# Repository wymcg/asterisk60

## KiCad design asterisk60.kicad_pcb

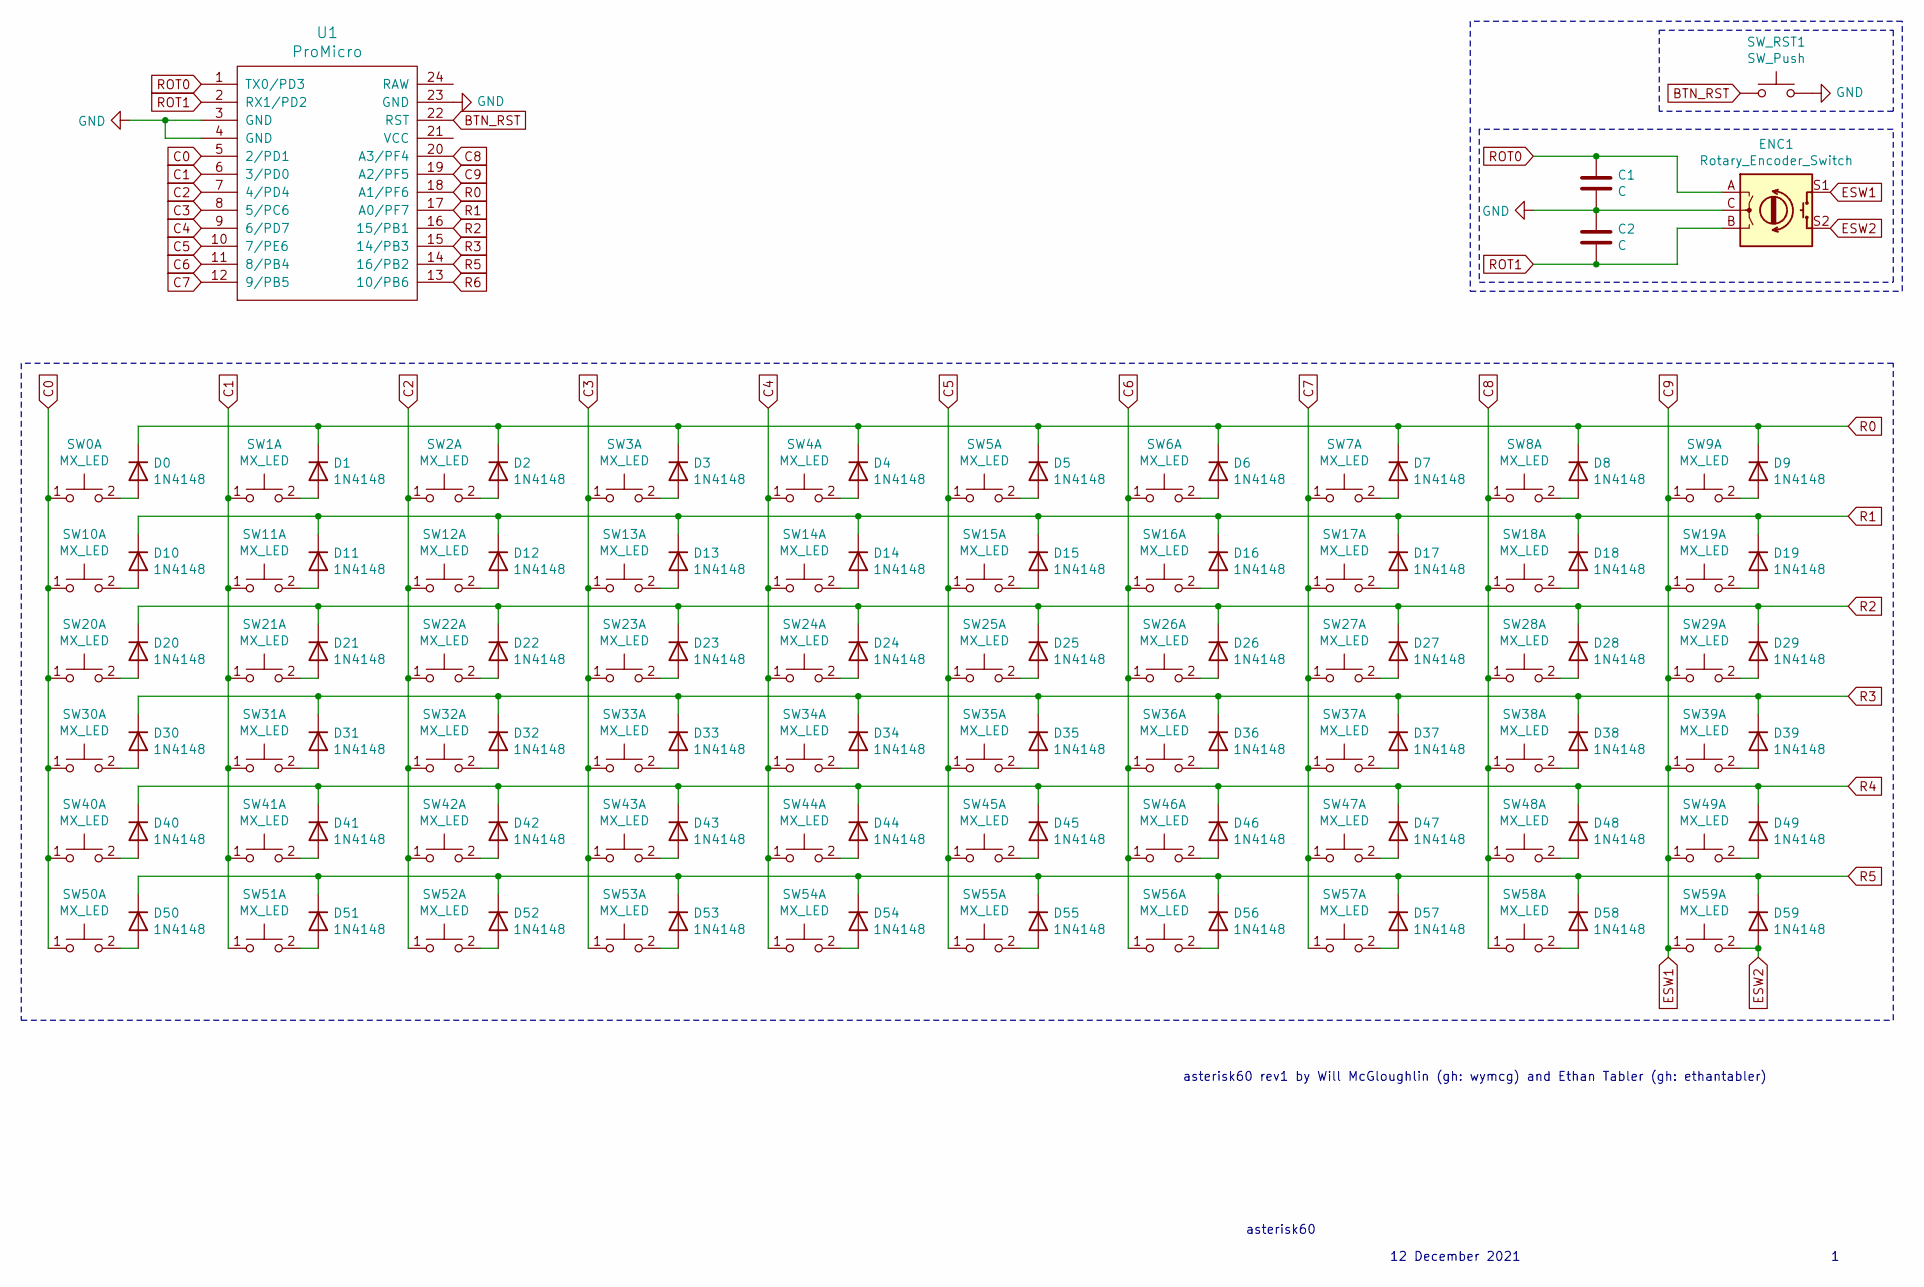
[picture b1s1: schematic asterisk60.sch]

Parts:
C1, C2: C; C_0603
D0, D1, D2, D3, D4, D5, D6, D7, D8, D9, D10, D11, D12, D13, D14, D15, D16, D17, D18, D19, D20, D21, D22, D23, D24, D25, D26, D27, D28, D29, D30, D31, D32, D33, D34, D35, D36, D37, D38, D39, D40, D41, D42, D43, D44, D45, D46, D47, D48, D49, D50, D51, D52, D53, D54, D55, D56, D57, D58, D59: 1N4148; D_DO-35_SOD27_P7.62mm_Horizontal
ENC1: Rotary_Encoder_Switch; RotaryEncoder_EC11
SW0, SW1, SW2, SW3, SW4, SW5, SW6, SW7, SW8, SW9, SW10, SW11, SW12, SW13, SW14, SW15, SW16, SW17, SW18, SW19, SW20, SW21, SW22, SW23, SW24, SW25, SW26, SW27, SW28, SW29, SW30, SW31, SW32, SW33, SW34, SW35, SW36, SW37, SW38, SW39, SW40, SW41, SW42, SW43, SW44, SW45, SW46, SW47, SW48, SW49, SW50, SW51, SW52, SW53, SW54, SW55, SW56, SW57, SW58, SW59: MX_LED; SW_Cherry_MX_1.00u_PCB
SW_RST1: SW_Push; SW_SPST_TL3342
U1: ProMicro; ArduinoProMicro

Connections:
BTN_RST: SW_RST1.1, U1.22 (RST)
C0: SW0.1, SW10.1, SW20.1, SW30.1, SW40.1, SW50.1, U1.5 (2/PD1)
C1: SW1.1, SW11.1, SW21.1, SW31.1, SW41.1, SW51.1, U1.6 (3/PD0)
C2: SW2.1, SW12.1, SW22.1, SW32.1, SW42.1, SW52.1, U1.7 (4/PD4)
C3: SW3.1, SW13.1, SW23.1, SW33.1, SW43.1, SW53.1, U1.8 (5/PC6)
C4: SW4.1, SW14.1, SW24.1, SW34.1, SW44.1, SW54.1, U1.9 (6/PD7)
C5: SW5.1, SW15.1, SW25.1, SW35.1, SW45.1, SW55.1, U1.10 (7/PE6)
C6: SW6.1, SW16.1, SW26.1, SW36.1, SW46.1, SW56.1, U1.11 (8/PB4)
C7: SW7.1, SW17.1, SW27.1, SW37.1, SW47.1, SW57.1, U1.12 (9/PB5)
C8: SW8.1, SW18.1, SW28.1, SW38.1, SW48.1, SW58.1, U1.20 (A3/PF4)
C9: ENC1.S1, SW9.1, SW19.1, SW29.1, SW39.1, SW49.1, SW59.1, U1.19 (A2/PF5)
ESW2: D59.2 (A), ENC1.S2, SW59.2
GND: C1.2, C2.1, ENC1.C, SW_RST1.2, U1.3 (GND), U1.4 (GND), U1.23 (GND)
unnamed: D0.2 (A), SW0.2
unnamed: D1.2 (A), SW1.2
unnamed: D2.2 (A), SW2.2
unnamed: D3.2 (A), SW3.2
unnamed: D4.2 (A), SW4.2
unnamed: D5.2 (A), SW5.2
unnamed: D6.2 (A), SW6.2
unnamed: D7.2 (A), SW7.2
unnamed: D8.2 (A), SW8.2
unnamed: D9.2 (A), SW9.2
unnamed: D10.2 (A), SW10.2
unnamed: D11.2 (A), SW11.2
unnamed: D12.2 (A), SW12.2
unnamed: D13.2 (A), SW13.2
unnamed: D14.2 (A), SW14.2
unnamed: D15.2 (A), SW15.2
unnamed: D16.2 (A), SW16.2
unnamed: D17.2 (A), SW17.2
unnamed: D18.2 (A), SW18.2
unnamed: D19.2 (A), SW19.2
unnamed: D20.2 (A), SW20.2
unnamed: D21.2 (A), SW21.2
unnamed: D22.2 (A), SW22.2
unnamed: D23.2 (A), SW23.2
unnamed: D24.2 (A), SW24.2
unnamed: D25.2 (A), SW25.2
unnamed: D26.2 (A), SW26.2
unnamed: D27.2 (A), SW27.2
unnamed: D28.2 (A), SW28.2
unnamed: D29.2 (A), SW29.2
unnamed: D30.2 (A), SW30.2
unnamed: D31.2 (A), SW31.2
unnamed: D32.2 (A), SW32.2
unnamed: D33.2 (A), SW33.2
unnamed: D34.2 (A), SW34.2
unnamed: D35.2 (A), SW35.2
unnamed: D36.2 (A), SW36.2
unnamed: D37.2 (A), SW37.2
unnamed: D38.2 (A), SW38.2
unnamed: D39.2 (A), SW39.2
unnamed: D40.2 (A), SW40.2
unnamed: D41.2 (A), SW41.2
unnamed: D42.2 (A), SW42.2
unnamed: D43.2 (A), SW43.2
unnamed: D44.2 (A), SW44.2
unnamed: D45.2 (A), SW45.2
unnamed: D46.2 (A), SW46.2
unnamed: D47.2 (A), SW47.2
unnamed: D48.2 (A), SW48.2
unnamed: D49.2 (A), SW49.2
unnamed: D50.2 (A), SW50.2
unnamed: D51.2 (A), SW51.2
unnamed: D52.2 (A), SW52.2
unnamed: D53.2 (A), SW53.2
unnamed: D54.2 (A), SW54.2
unnamed: D55.2 (A), SW55.2
unnamed: D56.2 (A), SW56.2
unnamed: D57.2 (A), SW57.2
unnamed: D58.2 (A), SW58.2
R0: D0.1 (K), D1.1 (K), D2.1 (K), D3.1 (K), D4.1 (K), D5.1 (K), D6.1 (K), D7.1 (K), D8.1 (K), D9.1 (K), U1.18 (A1/PF6)
R1: D10.1 (K), D11.1 (K), D12.1 (K), D13.1 (K), D14.1 (K), D15.1 (K), D16.1 (K), D17.1 (K), D18.1 (K), D19.1 (K), U1.17 (A0/PF7)
R2: D20.1 (K), D21.1 (K), D22.1 (K), D23.1 (K), D24.1 (K), D25.1 (K), D26.1 (K), D27.1 (K), D28.1 (K), D29.1 (K), U1.16 (15/PB1)
R3: D30.1 (K), D31.1 (K), D32.1 (K), D33.1 (K), D34.1 (K), D35.1 (K), D36.1 (K), D37.1 (K), D38.1 (K), D39.1 (K), U1.15 (14/PB3)
R4: D40.1 (K), D41.1 (K), D42.1 (K), D43.1 (K), D44.1 (K), D45.1 (K), D46.1 (K), D47.1 (K), D48.1 (K), D49.1 (K)
R5: D50.1 (K), D51.1 (K), D52.1 (K), D53.1 (K), D54.1 (K), D55.1 (K), D56.1 (K), D57.1 (K), D58.1 (K), D59.1 (K), U1.14 (16/PB2)
R6: U1.13 (10/PB6)
ROT0: C1.1, ENC1.A, U1.1 (TX0/PD3)
ROT1: C2.2, ENC1.B, U1.2 (RX1/PD2)

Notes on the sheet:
asterisk60
12 December 2021
asterisk60 rev1 by Will McGloughlin (gh: wymcg) and Ethan Tabler (gh: ethantabler)

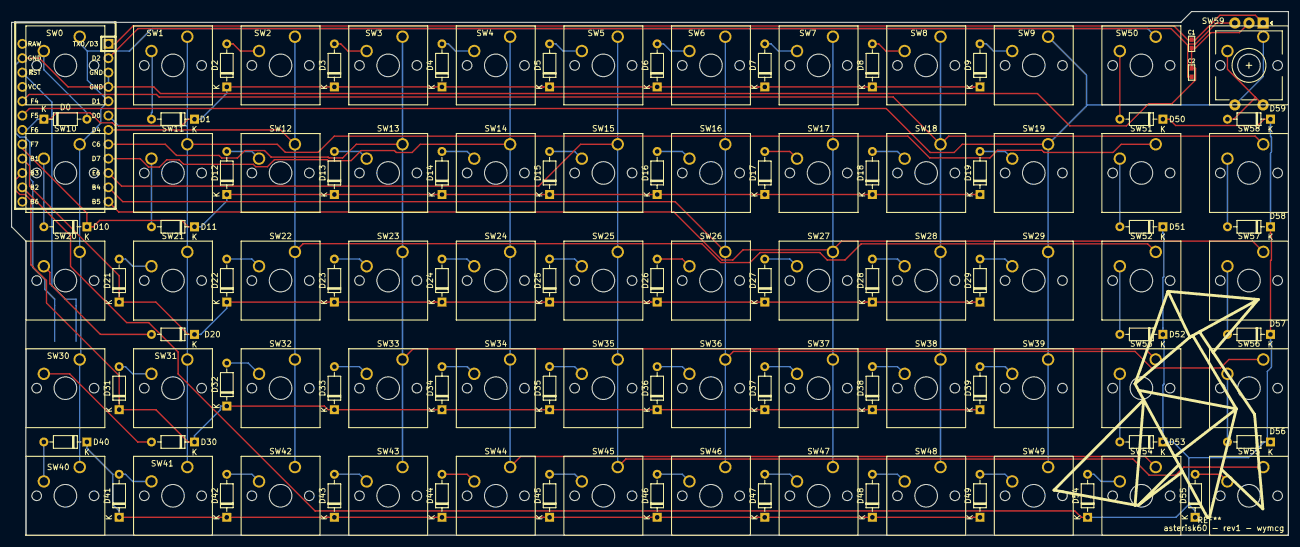
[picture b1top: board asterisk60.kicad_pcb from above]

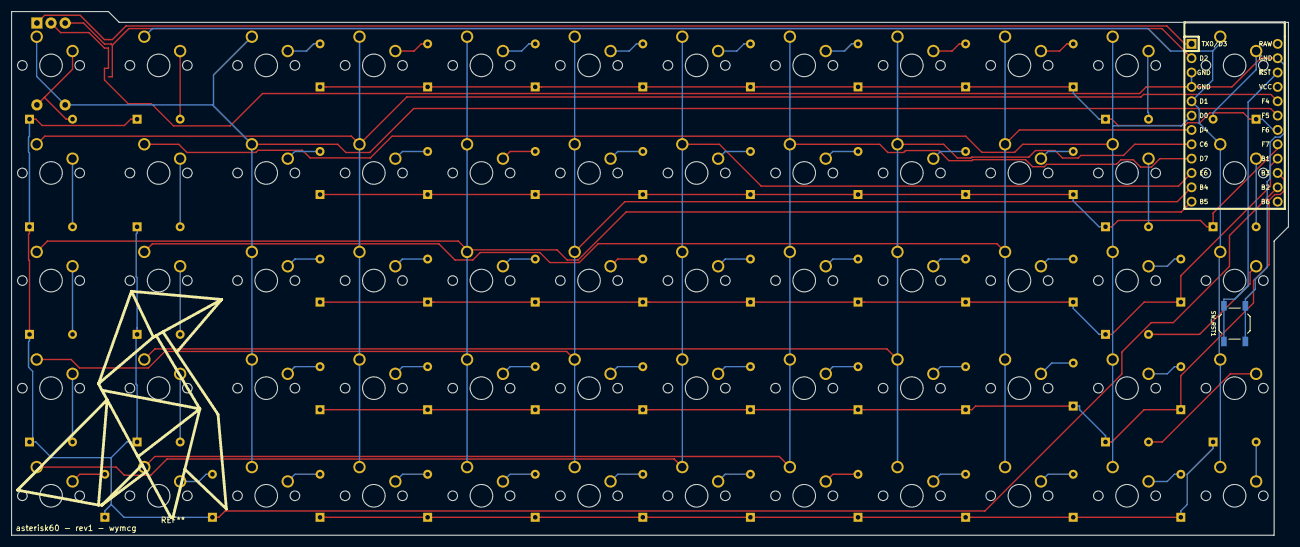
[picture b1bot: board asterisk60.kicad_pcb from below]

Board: 2 copper layers, 226.1 x 92.7 mm, 125 parts (2 on the bottom side), 80 nets.

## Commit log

2021-12-12 revamped pcb and added top and bottom plates
2021-12-12 logo added
2021-12-12 removed gerber files
